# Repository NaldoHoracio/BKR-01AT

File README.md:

# Projeto Final da Disciplina de Circuitos Impressos
## BKR-01AT

"Eu gostaria que fosse desenvolvido um equipamento que fosse capaz de medir as vibrações e a temperatura de um gerador em funcionamento. Vou chamá-lo de BKR:01AT. Acredito que, a partir dos dados obtidos, poderemos tirar algumas conclusões que podem aumentar o tempo de vida útil do equipamento. O equipamento deve enviar as leituras para uma central a qual já está pronta se comunica com os sensores em uma rede mesh."

Os equipamentos selecionados para desenvolver esse equipamento são:
- Acelerômetro: LIS2DHTR;
- MCU + Bluetooth: nRF52832-QFAB;
- LED indicativo de sistema ligado (livre escolha, cor verde)
- LED indicativo de problema de vibração detectado (livre escolha, cor vermelha)
- LED indicativo de problema de temperatura detectado (livre escolha, cor vermelha)
- Botão de reset (livre escolha, baixo custo)
- Botão de função 1 (livre escolha, baixo custo)
- Botão de função 2 (livre escolha, baixo custo)
- Alimentação por bateria CR2032 de 3,0V (não precisa comprar, mas precisa ter os furos para soldar a pilha)
- Outros componentes necessários são de livre escolha inclusive a antena;

Restrições:
1. A placa deve ter componentes de apenas um lado;
2. A logomarca da empresa deve aparecer na camada Silk na parte de baixo da placa (onde não tem componentes)
3. A placa tem que ter o formato quadrado nas dimensões 60x60mm
4. A placa deve ter furos de montagem nas quinas superior esquerda e inferior direito com diâmetro de 3,2mm e o centro do furo deve estar a 5mm das duas bordas;
5. A placa será montada por equipamentos automáticos portanto deve conter dois fiduciais posicionados na maior distância possível entre eles na placa;
6. O nome do projeto deve estar presente na parte frontal da placa acompanhado com a versão P1;
7. As bordas a placa devem ser arredondadas;
8. O resistores utilizados devem ser 0402;
9. O equipamento deve ter interface de gravação TC2030;
10. As trilhas de alimentação devem ter 12mil de espessuras e as de sinal 6mil;
11. O Clearence da placa deve ser de 6mil;
12. A trilha da antena deve ser calculada utilizando coplanar wave guide para obter uma impedância de 50 ohms;
13. A trilha deve ser protegida com um shielding por todo o seu comprimento e deve ser cercada por um plano de ground com stitching aplicado a ele.

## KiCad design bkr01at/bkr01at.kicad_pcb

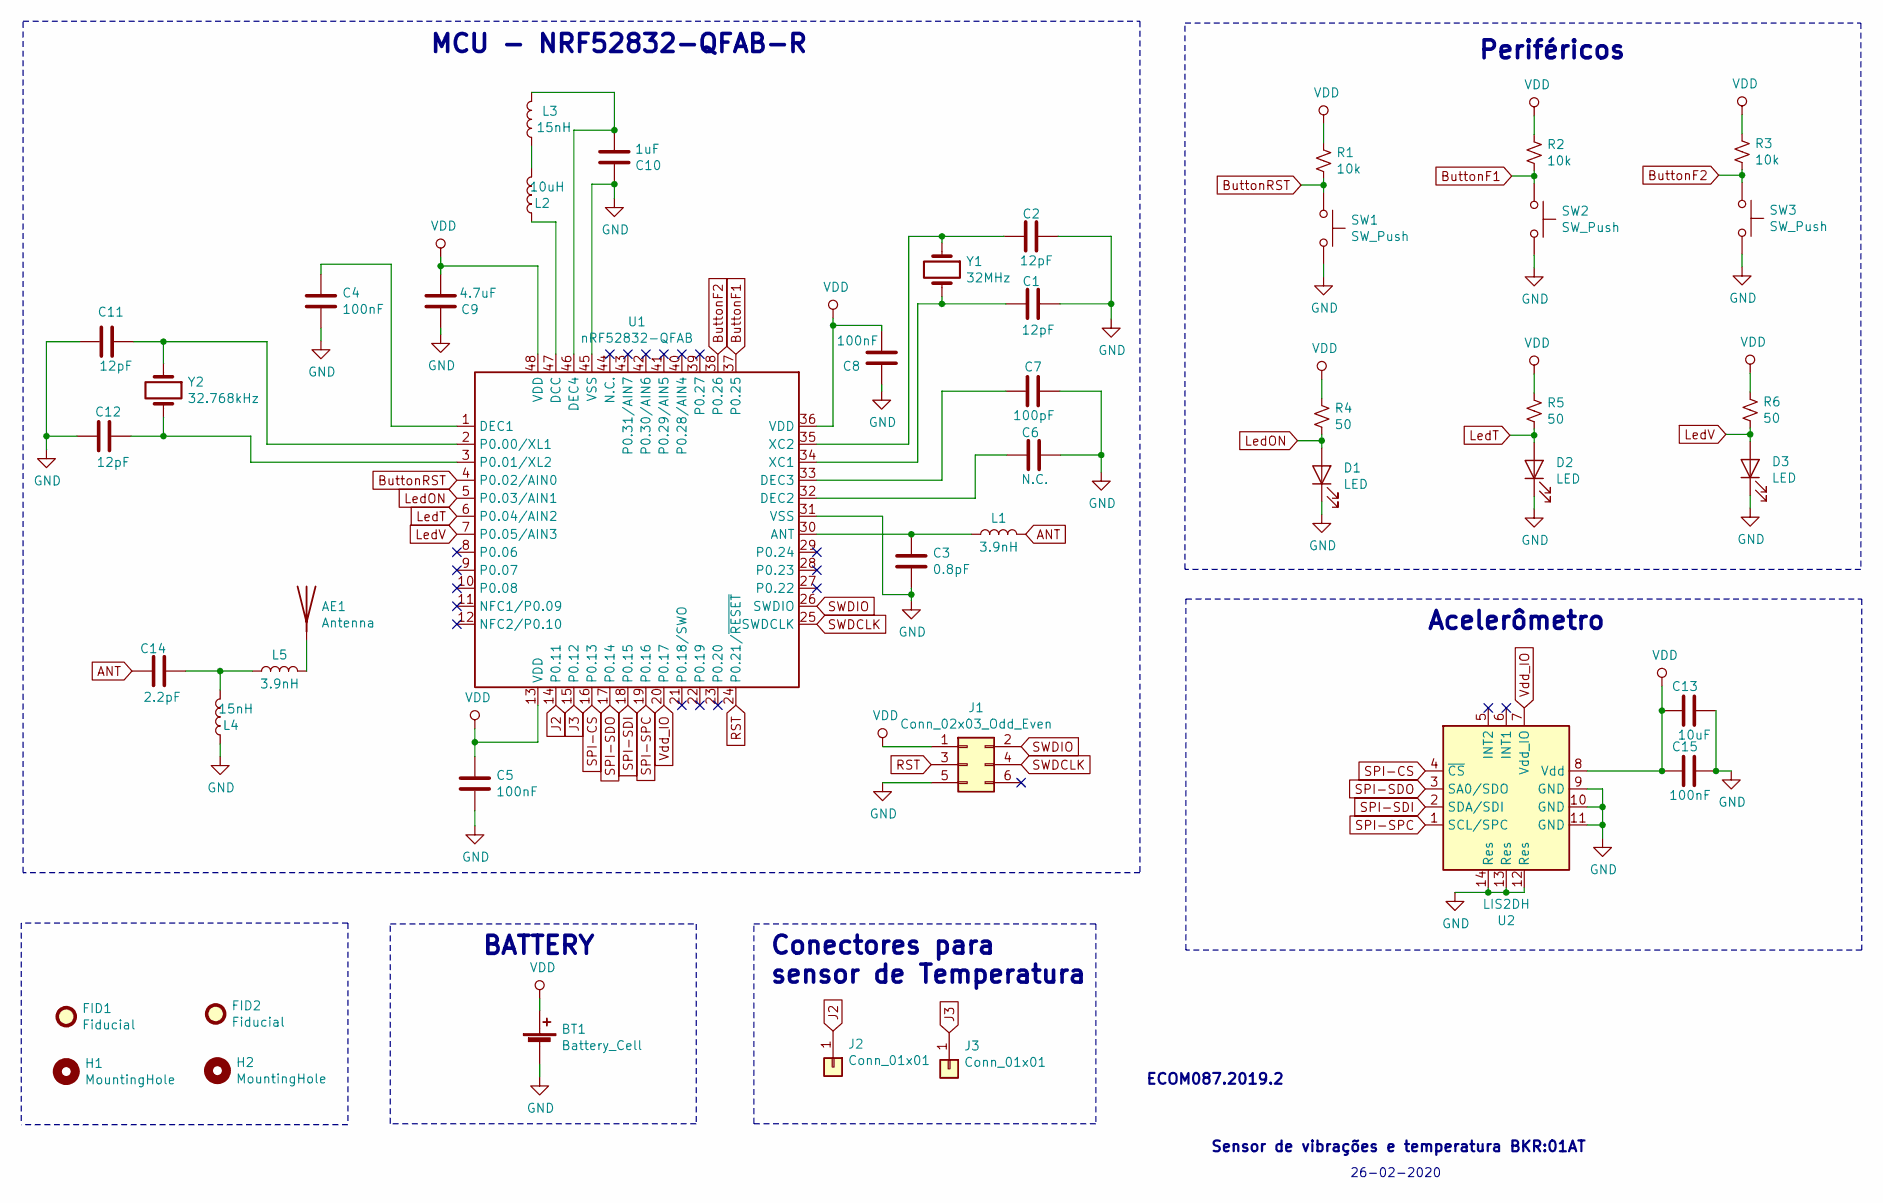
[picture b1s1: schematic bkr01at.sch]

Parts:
AE1: Antenna; 2450AT18B100
BT1: Battery_Cell; Battery_Panasonic_CR2032-VS1N_Vertical_CircularHoles
C1, C2, C11, C12: 12pF; C_0402_1005Metric
C3: 0.8pF; C_0402_1005Metric
C4, C5, C8, C15: 100nF; C_0402_1005Metric
C6: N.C.; C_0402_1005Metric
C7: 100pF; C_0402_1005Metric
C9: 4.7uF; C_0402_1005Metric
C10: 1uF; C_0402_1005Metric
C13: 10uF; C_0402_1005Metric
C14: 2.2pF; C_0402_1005Metric
D1, D2, D3: LED; LED_0603_1608Metric
FID1, FID2: Fiducial; Fiducial_0.5mm_Mask1.5mm
H1, H2: MountingHole; MountingHole_3.2mm_M3
J1: Conn_02x03_Odd_Even; Tag-Connect_TC2030-IDC-NL_2x03_P1.27mm_Vertical
J2, J3: Conn_01x01; SolderWirePad_1x01_Drill0.8mm
L1, L5: 3.9nH; L_0402_1005Metric
L2: 10uH; L_0402_1005Metric
L3, L4: 15nH; L_0402_1005Metric
R1, R2, R3: 10k; R_0402_1005Metric
R4, R5, R6: 50; R_0402_1005Metric
SW1, SW2, SW3: SW_Push; SW_MEC_5GSH9
U1: nRF52832-QFAB; QFN-48-1EP_6x6mm_P0.4mm_EP4.6x4.6mm
U2: LIS2DH; LGA-14_2x2mm_P0.35mm_LayoutBorder3x4y
Y1: 32MHz; Crystal_SMD_2016-4Pin_2.0x1.6mm
Y2: 32.768kHz; Crystal_SMD_3215-2Pin_3.2x1.5mm

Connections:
ANT: C14.1, L1.2
ButtonF1: R2.2, SW2.1, U1.37 (P0.25)
ButtonF2: R3.2, SW3.1, U1.38 (P0.26)
ButtonRST: R1.2, SW1.1, U1.4 (P0.02/AIN0)
GND: BT1.2 (-), C1.2, C2.2, C3.2, C4.2, C5.2, C6.2, C7.2, C8.1, C9.1, C10.1, C11.2, C12.2, C13.2, C15.2, D1.1 (K), D2.1 (K), D3.1 (K), J1.5, L4.1, SW1.2, SW2.2, SW3.2, U1.31 (VSS), U1.45 (VSS), U2.9 (GND), U2.10 (GND), U2.11 (GND), U2.12 (Res), U2.13 (Res), U2.14 (Res)
J2: J2.1, U1.14 (P0.11)
J3: J3.1, U1.15 (P0.12)
LedON: D1.2 (A), R4.2, U1.5 (P0.03/AIN1)
LedT: D2.2 (A), R5.2, U1.6 (P0.04/AIN2)
LedV: D3.2 (A), R6.2, U1.7 (P0.05/AIN3)
unnamed: AE1.1, L5.2
unnamed: C1.1, U1.34 (XC1), Y1.2
unnamed: C2.1, U1.35 (XC2), Y1.1
unnamed: C3.1, L1.1, U1.30 (ANT)
unnamed: C4.1, U1.1 (DEC1)
unnamed: C6.1, U1.32 (DEC2)
unnamed: C7.1, U1.33 (DEC3)
unnamed: C10.2, L3.2, U1.46 (DEC4)
unnamed: C11.1, U1.2 (P0.00/XL1), Y2.1
unnamed: C12.1, U1.3 (P0.01/XL2), Y2.2
unnamed: C14.2, L4.2, L5.1
unnamed: L2.1, U1.47 (DCC)
unnamed: L2.2, L3.1
RST: J1.3, U1.24 (P0.21/~RESET)
SPI-CS: U1.16 (P0.13), U2.4 (~CS)
SPI-SDI: U1.18 (P0.15), U2.2 (SDA/SDI)
SPI-SDO: U1.17 (P0.14), U2.3 (SA0/SDO)
SPI-SPC: U1.19 (P0.16), U2.1 (SCL/SPC)
SWDCLK: J1.4, U1.25 (SWDCLK)
SWDIO: J1.2, U1.26 (SWDIO)
VDD: BT1.1 (+), C5.1, C8.2, C9.2, C13.1, C15.1, J1.1, R1.1, R2.1, R3.1, R4.1, R5.1, R6.1, U1.13 (VDD), U1.36 (VDD), U1.48 (VDD), U2.8 (Vdd)
Vdd_IO: U1.20 (P0.17), U2.7 (Vdd_IO)

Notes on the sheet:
Sensor de vibrações e temperatura BKR:01AT
ECOM087.2019.2
26-02-2020
MCU - NRF52832-QFAB-R
Periféricos
Acelerômetro
BATTERY
Conectores para sensor de Temperatura

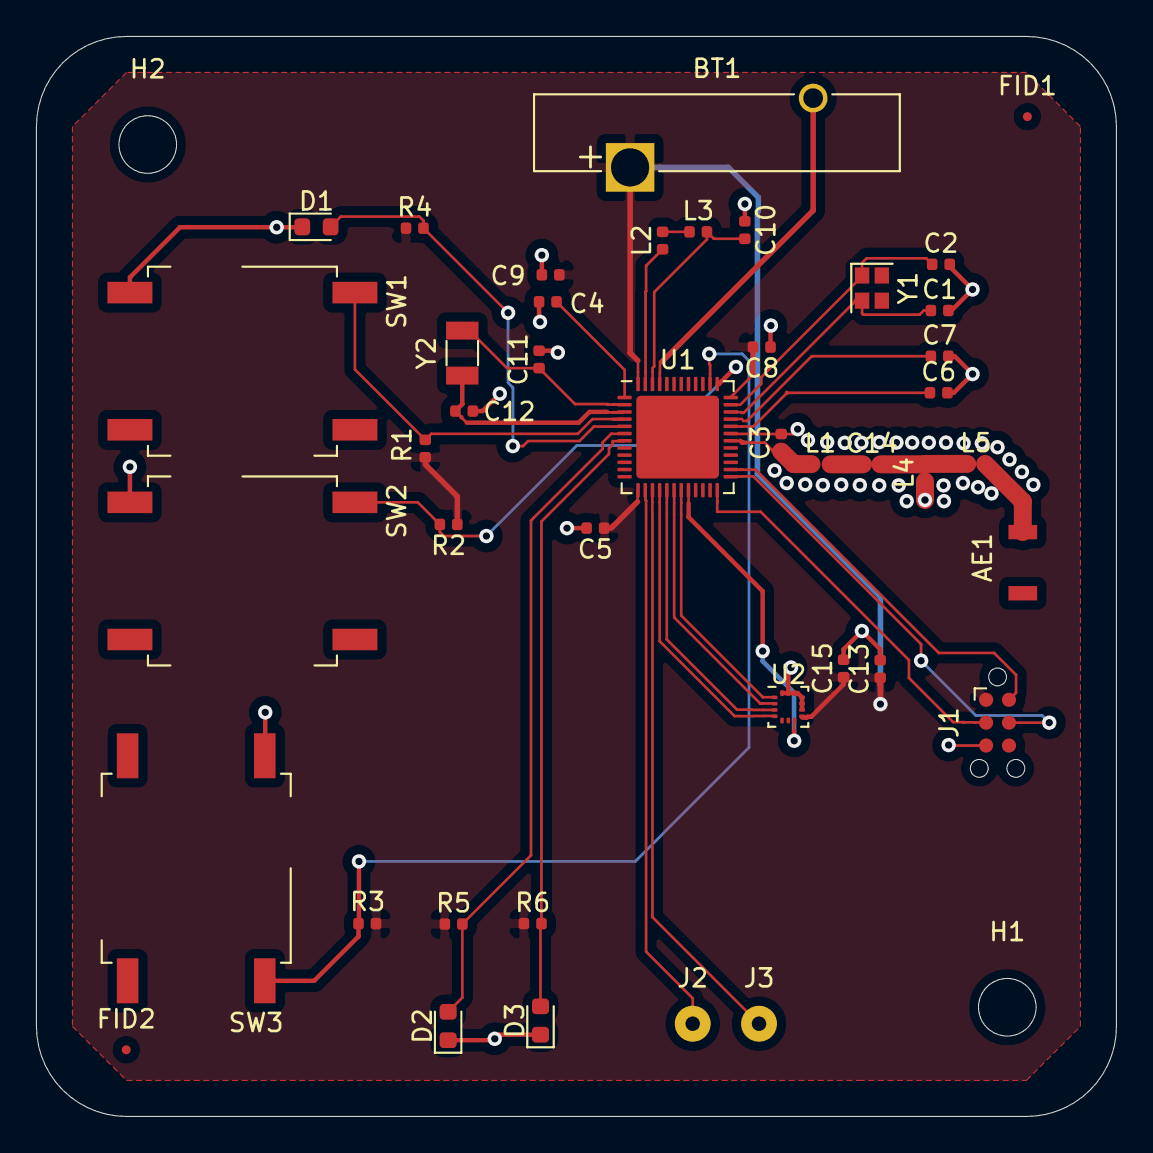
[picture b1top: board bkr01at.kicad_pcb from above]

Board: 2 copper layers, 60.0 x 60.0 mm, 45 parts (0 on the bottom side), 32 nets.

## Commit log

2020-02-16 Atualizando Readme.md
2020-02-27 Atualizando esquemático. Referências alocadas.
2020-02-28 Finalizando esquemático. Começando PCB.
2020-03-01 Atualizando esquemático.
2020-03-02 Esquemático ok. PCB is loading.
2020-03-02 Finalizando PCB.
2020-03-02 PCB e Esquemático finalizados.
